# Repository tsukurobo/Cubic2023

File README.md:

**目次**

- [Cubic2023](#cubic2023)
  - [概要](#概要)
    - [コメント](#コメント)
- [Cubic2023\_Shield](#cubic2023_shield)
  - [概要](#概要-1)
    - [encoder pull up](#encoder-pull-up)
    - [increment encoder cognition](#increment-encoder-cognition)
    - [inverter(NOT)](#inverternot)
    - [increment RP2040](#increment-rp2040)
    - [increment connecter](#increment-connecter)
    - [absolute encoder cognition](#absolute-encoder-cognition)
    - [absolute RP2040](#absolute-rp2040)
    - [absolute connector](#absolute-connector)
    - [decoupling capacitor](#decoupling-capacitor)
    - [Arduino nano 33 BLE](#arduino-nano-33-ble)
    - [to MotherBoard](#to-motherboard)
- [Cubic2023\_DCMotorDriver](#cubic2023_dcmotordriver)
  - [概要](#概要-2)
    - [connector](#connector)
    - [pull down](#pull-down)
    - [A3921](#a3921)
    - [current sensor](#current-sensor)
    - [Filter](#filter)
    - [DeadTime](#deadtime)
    - [Protection Circuit](#protection-circuit)
    - [for motor connection](#for-motor-connection)
    - [Bootstrap Chargepump](#bootstrap-chargepump)
    - [Indication Circuit](#indication-circuit)
    - [V5 Circuit](#v5-circuit)
    - [Decoupling Condenser](#decoupling-condenser)
    - [Bridge](#bridge)
    - [pull up](#pull-up)
    - [error lamp](#error-lamp)
    - [PS](#ps)
    - [BD63150](#bd63150)
    - [Protection Circuit](#protection-circuit-1)
    - [Indication Circuit](#indication-circuit-1)
    - [VREF](#vref)
    - [for solenoid valve](#for-solenoid-valve)
- [Cubic2023\_RP2040](#cubic2023_rp2040)
  - [概要](#概要-3)
    - [RP2040](#rp2040)
    - [bypass condenser](#bypass-condenser)
    - [surge protection](#surge-protection)
    - [connector](#connector-1)
    - [indicator](#indicator)
    - [RESET switch](#reset-switch)
    - [microUSB](#microusb)
    - [QSPI NOR flash](#qspi-nor-flash)
    - [crystal](#crystal)

# Cubic2023

## 概要
つくばろぼっとサークルではNHK学生ロボコンに向けて統合型基板を製作しており、mainがNHK学生ロボコン2023において使用したバージョンです。
回路図の説明やブロック分けなどが出来ておらず、分かりにくい状態です。※修正中

### コメント
修正中です。8/10程度を目途に進めています。

# Cubic2023_Shield
## 概要
メインマイコンを搭載する基板です。メインマイコンには以下の理由からArduino nano 33 BLE(以下：AN33BLE)を採用しました。
- 32bitマイコン
- 浮動小数点演算ユニット搭載
- 書き込み環境の構築が容易

また、AN33BLEはIMUを搭載している点もメリットです。実際には用いていないため精度は不明ですが、基板面積という点では確実にプラスです。

センサとしては、8つのインクリメンタルエンコーダと8つのアブソリュートエンコーダを接続できるように設計しました。

### encoder pull up
インクリメントエンコーダに接続しているA相B相Z相をプルアップしています。

### increment encoder cognition
インクリメントエンコーダは、Z相の多くの範囲でLOWを返すため、NOT回路によりHIGHになり、LEDが光る仕組みです。Z相をプルアップしてるため、未接続の場合LEDは光りません。A相B相が断線してる場合、LEDは光りますが正常に認識されるとは限りません。何番のエンコーダに接続してるか簡易的に確認するための機能です。

### inverter(NOT)
インクリメントエンコーダの波形を整形するインバータ（バッファ）です。NOT回路と等価なので信号が反転します。A相B相は反転しても大きな影響はないですが、Z相はhighの時間が長くなります。長い信号線を介してセンシングするためチャタリング防止などの観点から挿入しました。また、5VトレラントのICを介することで5V信号を3.3Vで駆動するRP2040に入力できるようにしています。

### increment RP2040
インクリメントエンコーダを読み取り値を記録、メインマイコンの要求に応じて状態を返すためのマイコンです。インクリメントエンコーダの読み取りは割り込み処理を必要とするため、メインマイコンと分離したいと考え、この設計にしました。

### increment connecter
ラッチ付かつサイズが小さいコネクタが望ましかったため、PAコネクタを採用しました。**AMT102/103**を接続することを想定して、ピンの順番を設定しています。

### absolute encoder cognition
アブソリュートエンコーダとのSPI通信が確立した場合にRP2040がGPIOを操作しLEDを点灯させることが出来るようにしました。

### absolute RP2040
アブソリュートエンコーダと通信をして値を記録、メインマイコンの要求に応じて状態を返すためのマイコンです。メインマイコンをmasterとしたSPIバスとは別に、absolute RP2040をmasterとしたエンコーダとの通信用のSPIバスを用意しています。

### absolute connector
こちらもPAコネクタを採用しています。**AMT223**を接続することを想定して、ピンの順番を設定しています。

### decoupling capacitor
基板上のICなどのバイパスコンデンサです。配線を引き延ばすためエンコーダのコネクタ近くにも配置しました。

### Arduino nano 33 BLE
メインマイコンです。enableをHIGHにすることでシステムを起動することができます。RESETをLOWにすることでエンコーダ用のRP2040をリセットさせることできます。他はSPI通信用のGPIOです。

### to MotherBoard
電源、SPI通信、シャットダウン信号を共有しています。

### emergency shutdown
緊急停止スイッチ接続することでシステムを起動できます。LEDにより起動状態を表示しています。

### 3-state buffer
SPI通信のslave側は通信していないときはMISOをオープンにする仕様ですが、RP2040はLOWを出力してしまい、複数slave運用がデフォルトで不可能であったため、3-state bufferを付加することで対策しました。

# Cubic2023_DCMotorDriver
## 概要
RZ-735クラスのDCモータを2基、RS-555クラスのDCモータを1基、24Vで駆動することが出来る基板です。以下ではRZ-735を想定したチャネルをメインチャネル、他方をサブチャネルと呼称します。

メインチャネルではICにA3921を採用しています。サブチャネルではICにBD63150を採用しています。データシートを参考に作成しました。データシートに載っている内容は説明を省略します。

サブチャネルはハーフブリッジ×2と見なすことで電磁弁を制御することも出来ます。

https://www.allegromicro.com/ja-jp/products/motor-drivers/brush-dc-motor-drivers/a3921

https://www.rohm.co.jp/products/motor-actuator-drivers/dc-brush-motor/bd63150afm-product

### connector
電流センサのアナログ値伝送用に4pin、信号・降圧電源用に14pin、VDDとGNDPWRに各14pinでMotherBoardと接続します。GNDは信号用と電源用で分離しています。

### pull down
MotherBoardからの信号がない場合の誤動作防止のためにプルダウン抵抗を挿入しています。

### A3921
Cissの大きいMOSFETを容易に駆動できる便利なICです。SR,PWMLにhighを入力、pwmhにPWM、phaseにhigh/lowを入力することで、SMB方式でモータを駆動できます。

### current sensor
メインチャネルを電流制御するために搭載した電流センサICです。コスト面からACS712を採用しましたが、動作を確認したところ、ノイズの影響で大きかったため、現状電流を用いた制御は実装していません。

### Filter
MotherBoardに大容量の電解コンデンサを搭載していますが、ピンヘッダを経由するため補助として中容量の電解コンデンサを搭載しています。

### DeadTime
$$ 50+\frac{7200}{1.2+(200/Rdead[kΩ])} $$
datasheet上の数式に従いdeadtimeが2300nsになるように抵抗値を設定しました。

### Protection Circuit
RCスナバ回路と双方向ツェナーダイオードによる保護回路を搭載しています。RCスナバ回路の値は以下の式に基づいて決定しました。回路を解析して搭載したわけではなく、簡易的な計算から求めているため効果は薄いと思います。

$$ Rsnb = \frac{Vin}{Iin} = \frac{24[V]}{2.4[A]} = 10[Ω] $$
$$ Csnb = \frac{Prsnb}{f×{Vin}^2} = \frac{0.1[W]}{60k[Hz]×{24[V]}^2} = 2.89n[F] $$

$$ Iin:想定電流, Prsnb：スナバ抵抗の定格電力, f:MD動作周波数$$
※想定電流は実際より小さめ、MD動作周波数は実際より大きめの値で計算されてます。設計初期の名残です。

モーターの逆起電力からMDを保護するために降伏電圧が28Vの双方向ツェナーダイオード（TVS）を採用しています。

**注：現行基板では、逆起電力から保護しきれていないことが原因と思われるA3921の破壊が確認されています。**

### for motor connection
モーターに接続する端子です。

### Bootstrap Chargepump
DCバイアスを考慮してコンデンサを配置しました。

### Indication Circuit
モーターに接続している箇所にLEDを対面配置することで回転方向を表示しています。プログラム開発時に便利でした。ローサイドMOSFETのゲート端子にデバッグ用のLEDを配置しています。ICが壊れた場合に表示されなくなるのでデバッグに活用できました。

|  LEDの色  |  用途  |
| ---- | ---- |
|  緑  |  常時点灯  |
|  青  |  電源ON＆正常時点灯  |
|  赤  |  異常時点灯  |
|  黄  |  状態表示  |
|  白  |  状態表示  |

### V5 Circuit
A3921に搭載されている5Vレギュレータを利用してA3921搭載のエラーLEDを配置しています。また、VDSTHに送る電圧を分圧で生成しています。

### Decoupling Condenser
ブートストラップコンデンサの容量が大きく、A3921の挙動が不安定になることがあったので、10uFのコンデンサを搭載しました。

### Bridge
フルブリッジ回路です。前述のRCスナバ回路を搭載しています。MOSFETは**RJ1L12BGN**を採用しています。corestaffで購入すると比較的安価に購入可能です。ON抵抗は小さいですが、ゲート容量は大きいので気を付けてください。新規設計する場合は**RS6L120BG**がおすすめです。ゲート抵抗には27Ωを採用しました。この抵抗値にした理由は勘です。

簡易的ではありますが以下の式で計算可能です。
$$ \frac{Vg}{Imax} < Rg < \frac{Tdead}{3×Ciss}$$
$$ Rg:ゲート抵抗,Vg:ゲート駆動電圧,Imax:ICがゲートに流せる最大電流,Tdead:デッドタイム,Ciss:MOSFET入力容量　$$
※条件によっては解なしになるかと思います。

### pull up
MDへの入力信号をプルアップしています。

### error lamp
BD63150のエラー表示用のLEDです。

### PS
PowerSaveに繋いでる端子です。プルアップしています。

### BD63150
電圧制御・電流制限に対応したモータードライバICです。RFNには100mΩのシャント抵抗を搭載しています。3Aで電流制限をする計算でしたが、想定より厳しめに作動していました。恐らくGNDを信号とパワーで分離した弊害だと思われます。

### Protection Circuit
メインチャネルと同様の構成です。

### Indication Circuit
メインチャネルと同様の構成です。

### VREF
電流の制限値をICに入力するピンです。3Aで制限するように設定したのですが、前述の通り思うように動きませんでした。

### for solenoid valve
電磁弁を駆動できるように付加した回路です。セーフティとしてリセッタブルヒューズを載せています。また還流ダイオードも載せています。

# Cubic2023_RP2040
## 概要
Cubicでは以下の理由から組み込みマイコンにRP2040を採用しました。
- GPIOとPWMが多い
- cortex-M0（計算速度がそこそこ速い）
- 安価
- 書き込みが容易

システム内で3つ使い、容易に交換可能とするためにマイコンボードとして最小構成の基板を作成しました。

以下の公式リファレンスを参考に作成しました。公式リファレンスに載っている内容は説明を省略します。
https://datasheets.raspberrypi.com/rp2040/hardware-design-with-rp2040.pdf

### RP2040
RP2040と周辺の配線です。
### bypass condenser
マイコンの電力消費が多く動作が不安定になることがあったため、100uFのセラコンを追加しています。
### surge protection
システム内でモータドライバと絶縁せずにRP2040を用いている箇所があるため、サージ保護としてツェナーダイオードを電源に並列に繋いでいます。
### connector
基板サイズの制約の中でGPIOをフルに使う必要があり、1.27mmピッチのピンヘッダを採用しました。配線の最適化と差し込みの一意性を担保するために基板の3辺に沿うように配置しています。
### indicator
基板内通信にSPIを利用しているのですが、SPI通信の状態を外部から容易に観測するためにslave側のSSに該当する箇所にLEDを付けています。以下は目視のLED状態とSSに注意したSPI通信の状況です。
|  LED  |  状況  |
| ---- | ---- |
|  点灯  |  通信異常  |
|  僅かに点灯  |  正常  |
|  点滅  |  通信速度低  |
|  消灯  |  オフライン  |

### RESET switch
RP2040をリセットできます。接続先がMotherBoardの場合は、接続先もリセットされます。

### microUSB
RP2040にプログラムを書き込むmicroUSBです。基本的に動作中の電源は接続先の基板から受け取るため、RP2040に書き込む以外は使用しない想定です。

### QSPI NOR flash
プログラムが書き込まれるメモリです。

### crystal
RP2040動作のためのcrystalです。

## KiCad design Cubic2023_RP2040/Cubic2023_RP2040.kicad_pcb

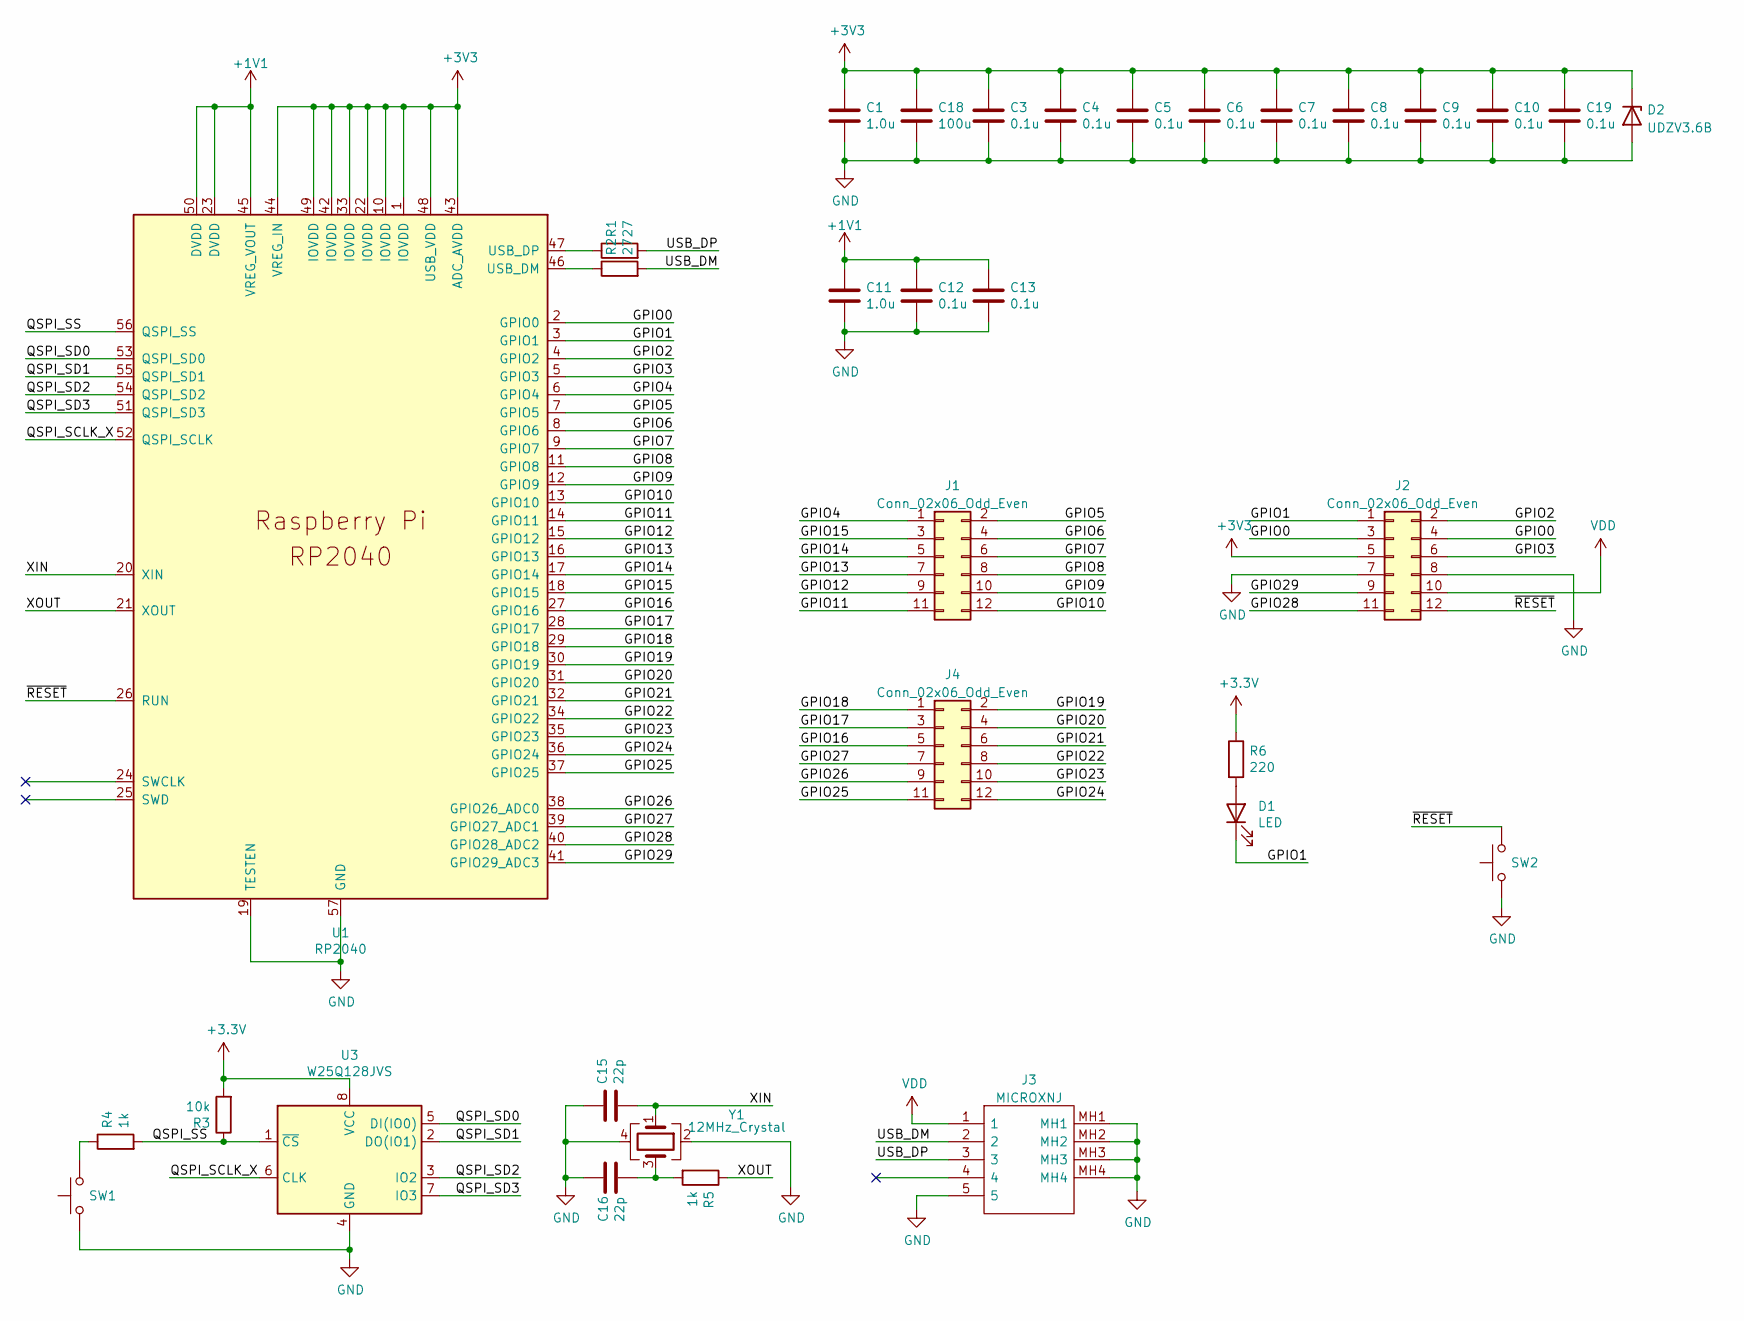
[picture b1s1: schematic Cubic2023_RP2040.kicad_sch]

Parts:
C1, C11: 1.0u; C_0805_2012Metric; LCSC C28323
C3, C4, C5, C6, C7, C8, C9, C10, C12, C13, C19: 0.1u; C_0402_1005Metric_Pad0.74x0.62mm_HandSolder; LCSC C307331
C15, C16: 22p; C_0402_1005Metric_Pad0.74x0.62mm_HandSolder; LCSC C1555
C18: 100u; C_1206_3216Metric; LCSC C15008
D1: LED; LED_0603_1608Metric_Pad1.05x0.95mm_HandSolder; LCSC C72041
D2: UDZV3.6B; D_SOD-323_HandSoldering
J1, J2, J4: Conn_02x06_Odd_Even; PinHeader_2x06_P1.27mm_Vertical
J3: MICROXNJ; Manufacturer_Part_Number MICROXNJ; LCSC C404969
R1, R2: 27; R_0603_1608Metric; LCSC C25190
R3: 10k; R_0603_1608Metric; LCSC C25804
R4, R5: 1k; R_0603_1608Metric; LCSC C21190
R6: 220; R_0603_1608Metric; LCSC C22962
SW1, SW2: SW_Push; SW_DIP_SPSTx01_Slide_9.78x4.72mm_W7.62mm_P2.54mm
U1: RP2040; RP2040-QFN-56; LCSC C2040
U3: W25Q128JVS; SOIC-8_5.23x5.23mm_P1.27mm; LCSC C97521
Y1: 12MHz_Crystal; Crystal_SMD_3225-4Pin_3.2x2.5mm; LCSC C9002

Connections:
+1V1: C11.1, C12.1, C13.1, U1.23 (DVDD), U1.45 (VREG_VOUT), U1.50 (DVDD)
/GPIO0: J2.3, J2.4, U1.2 (GPIO0)
/GPIO1: D1.1 (K), J2.1, U1.3 (GPIO1)
/GPIO2: J2.2, U1.4 (GPIO2)
/GPIO3: J2.6, U1.5 (GPIO3)
/GPIO4: J1.1, U1.6 (GPIO4)
/GPIO5: J1.2, U1.7 (GPIO5)
/GPIO6: J1.4, U1.8 (GPIO6)
/GPIO7: J1.6, U1.9 (GPIO7)
/GPIO8: J1.8, U1.11 (GPIO8)
/GPIO9: J1.10, U1.12 (GPIO9)
/GPIO10: J1.12, U1.13 (GPIO10)
/GPIO11: J1.11, U1.14 (GPIO11)
/GPIO12: J1.9, U1.15 (GPIO12)
/GPIO13: J1.7, U1.16 (GPIO13)
/GPIO14: J1.5, U1.17 (GPIO14)
/GPIO15: J1.3, U1.18 (GPIO15)
/GPIO16: J4.5, U1.27 (GPIO16)
/GPIO17: J4.3, U1.28 (GPIO17)
/GPIO18: J4.1, U1.29 (GPIO18)
/GPIO19: J4.2, U1.30 (GPIO19)
/GPIO20: J4.4, U1.31 (GPIO20)
/GPIO21: J4.6, U1.32 (GPIO21)
/GPIO22: J4.8, U1.34 (GPIO22)
/GPIO23: J4.10, U1.35 (GPIO23)
/GPIO24: J4.12, U1.36 (GPIO24)
/GPIO25: J4.11, U1.37 (GPIO25)
/GPIO26: J4.9, U1.38 (GPIO26_ADC0)
/GPIO27: J4.7, U1.39 (GPIO27_ADC1)
/GPIO28: J2.11, U1.40 (GPIO28_ADC2)
/GPIO29: J2.9, U1.41 (GPIO29_ADC3)
/QSPI_SCLK_X: U1.52 (QSPI_SCLK), U3.6 (CLK)
/QSPI_SD0: U1.53 (QSPI_SD0), U3.5 (DI(IO0))
/QSPI_SD1: U1.55 (QSPI_SD1), U3.2 (DO(IO1))
/QSPI_SD2: U1.54 (QSPI_SD2), U3.3 (IO2)
/QSPI_SD3: U1.51 (QSPI_SD3), U3.7 (IO3)
/QSPI_SS: R3.1, R4.2, U1.56 (QSPI_SS), U3.1 (~CS)
/USB_DM: J3.2, R2.2
/USB_DP: J3.3, R1.2
/XIN: C15.2, U1.20 (XIN), Y1.1
/XOUT: R5.1, U1.21 (XOUT)
/~RESET: J2.12, SW2.2, U1.26 (RUN)
GND: C1.2, C3.2, C4.2, C5.2, C6.2, C7.2, C8.2, C9.2, C10.2, C11.2, C12.2, C13.2, C15.1, C16.1, C18.2, C19.2, D2.2 (A), J2.7, J2.8, J3.5, J3.MH1, J3.MH2, J3.MH3, J3.MH4, SW1.1, SW2.1, U1.19 (TESTEN), U1.57 (GND), U3.4 (GND), Y1.2, Y1.4
unnamed: D1.2 (A), R6.2
unnamed: R1.1, U1.47 (USB_DP)
unnamed: R2.1, U1.46 (USB_DM)
unnamed: R4.1, SW1.2
unnamed: C16.2, R5.2, Y1.3
VDD: J2.10, J3.1

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
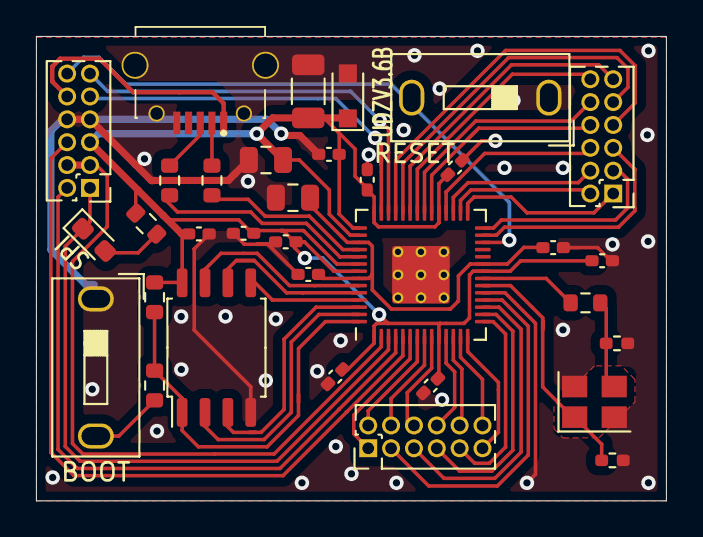
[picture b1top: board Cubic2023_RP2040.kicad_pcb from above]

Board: 2 copper layers, 35.0 x 25.8 mm, 33 parts (0 on the bottom side), 50 nets.

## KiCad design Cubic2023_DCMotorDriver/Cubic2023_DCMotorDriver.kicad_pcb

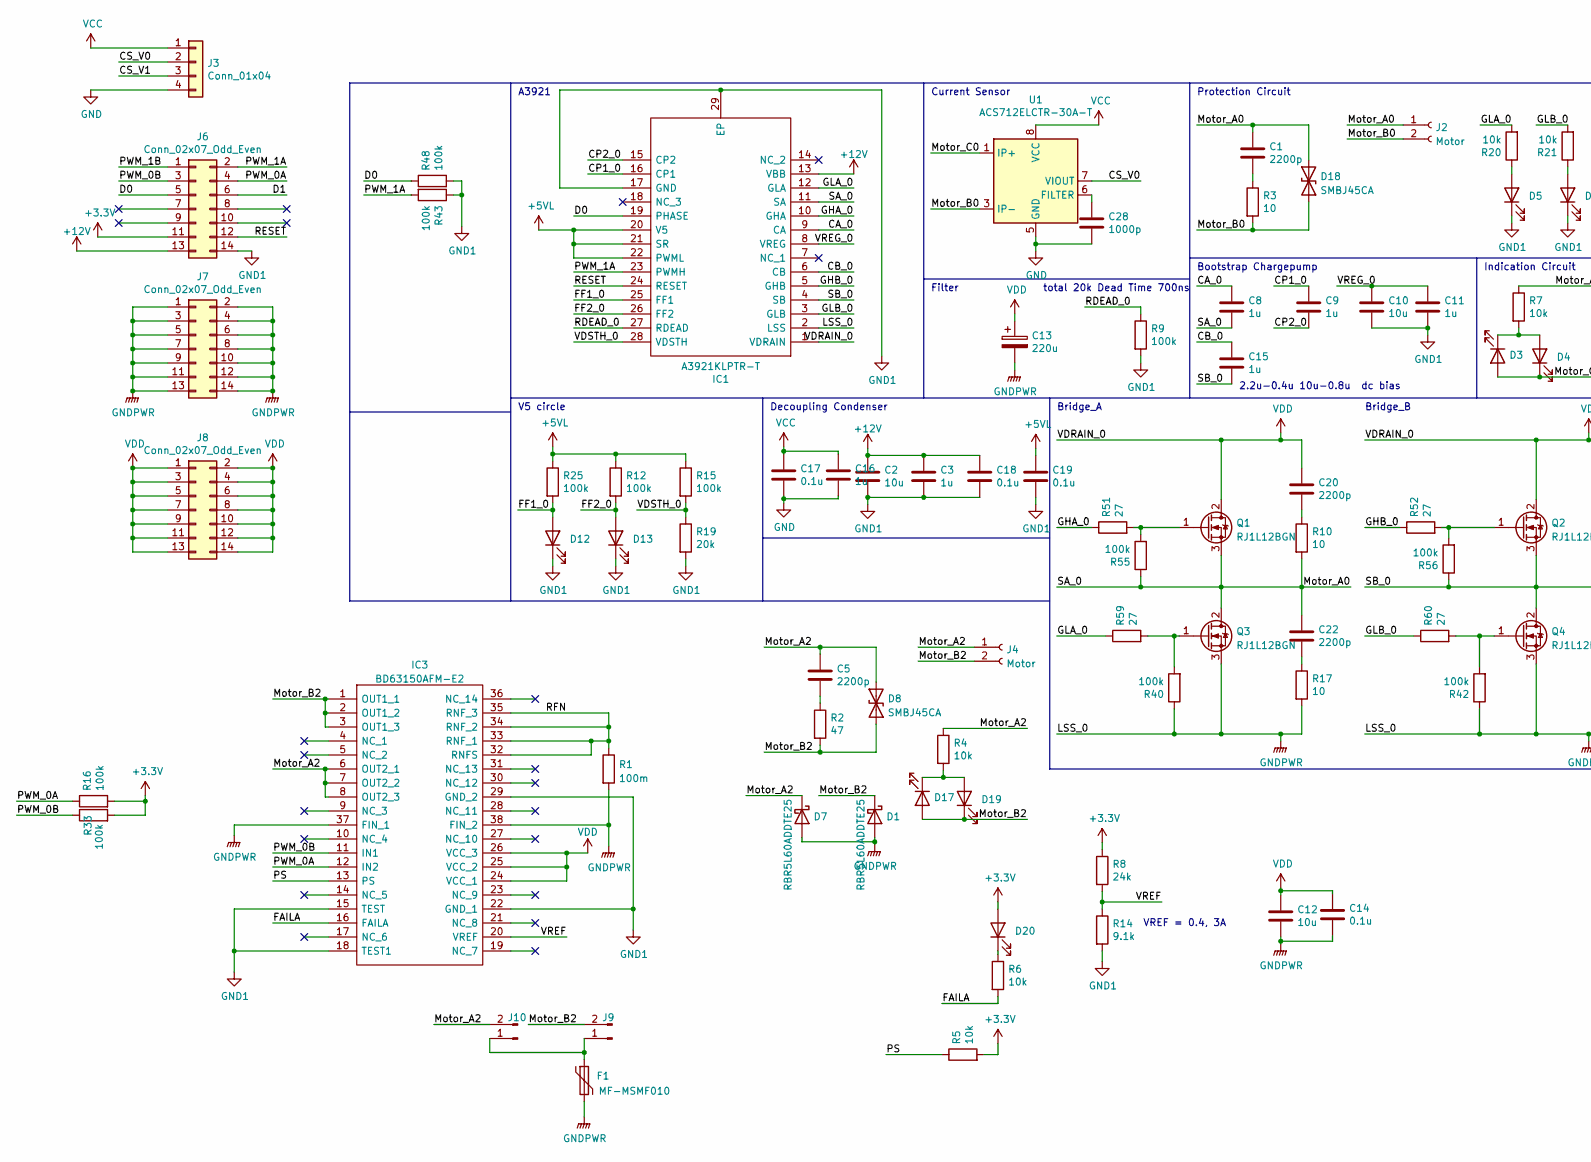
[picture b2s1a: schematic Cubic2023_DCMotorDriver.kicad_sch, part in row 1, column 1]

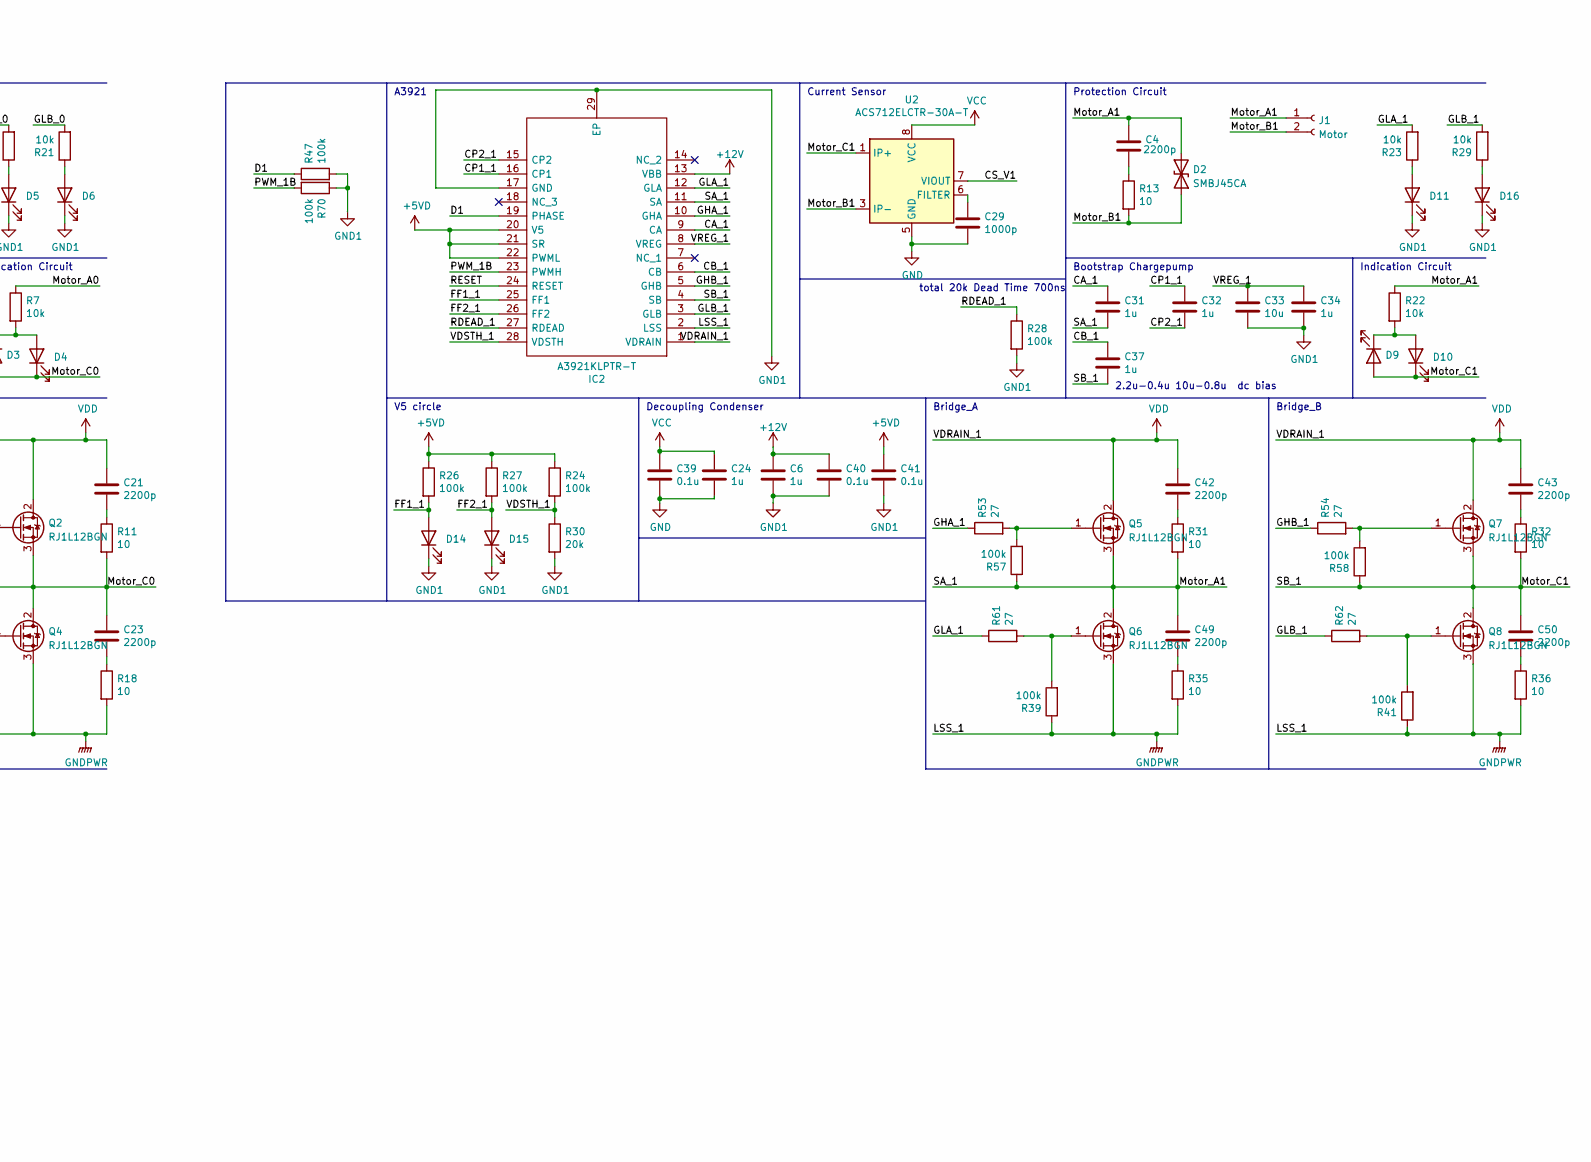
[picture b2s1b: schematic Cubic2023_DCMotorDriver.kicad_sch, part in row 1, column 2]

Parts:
C1, C4, C5, C20, C21, C22, C23, C42, C43, C49, C50: 2200p; R_0603_1608Metric; LCSC C1604
C2, C10, C12, C33: 10u; C_1206_3216Metric; LCSC C13585
C3, C6, C8, C9, C11, C15, C16, C24, C31, C32, C34, C37: 1u; R_0603_1608Metric; LCSC C15849
C13: 220u; CP_Elec_10x10.5
C14, C17, C18, C19, C39, C40, C41: 0.1u; C_0402_1005Metric_Pad0.74x0.62mm_HandSolder; LCSC C307331
C28, C29: 1000p; R_0603_1608Metric; LCSC C1588
D1, D7: RBR5L60ADDTE25; D_SMA
D2, D8, D18: SMBJ45CA; D_SMB; LCSC C353357
D3, D9, D17: LED_White; D_0603_1608Metric_Pad1.05x0.95mm_HandSolder; LCSC C2290
D4, D10, D19: LED_Yellow; D_0603_1608Metric_Pad1.05x0.95mm_HandSolder; LCSC C72038
D5, D6, D11, D16: LED_Blue; D_0603_1608Metric_Pad1.05x0.95mm_HandSolder; LCSC C72041
D12, D13, D14, D15, D20: LED_Red; D_0603_1608Metric_Pad1.05x0.95mm_HandSolder; LCSC C2286
F1: MF-MSMF010; Fuse_1812_4532Metric; LCSC C12430
IC1, IC2: A3921KLPTR-T; HTSSOP-28-1EP_4.4x9.7mm_P0.65mm_EP2.85x5.4mm_ThermalVias; Manufacturer_Part_Number A3921KLPTR-T
IC3: BD63150AFM-E2; BD63150AFME2; Manufacturer_Part_Number BD63150AFM-E2; Mouser Part Number 755-BD63150AFM-E2
J1, J2, J4: Motor; T_plug_female
J3: Conn_01x04; PinHeader_1x04_P2.54mm_Horizontal
J6, J7, J8: Conn_02x07_Odd_Even; PinHeader_2x07_P2.54mm_Horizontal
J9, J10: Conn_01x02_Male; PinHeader_1x02_P2.00mm_Horizontal
Q1, Q2, Q3, Q4, Q5, Q6, Q7, Q8: RJ1L12BGN; TO-263-2
R1: 100m; R_2512_6332Metric; LCSC C2994646
R2: 47; R_0603_1608Metric; LCSC C23182
R3, R10, R11, R13, R17, R18, R31, R32, R35, R36: 10; R_0603_1608Metric; LCSC C22859
R4, R5, R6, R7, R20, R21, R22, R23, R29: 10k; R_0603_1608Metric; LCSC C25804
R8: 24k; R_0603_1608Metric; LCSC C23352
R9, R12, R15, R16, R24, R25, R26, R27, R28, R33, R39, R40, R41, R42, R43, R47, R48, R55, R56, R57, R58, R70: 100k; R_0603_1608Metric; LCSC C25803
R14: 9.1k; R_0603_1608Metric; LCSC C23260
R19, R30: 20k; R_0603_1608Metric; LCSC C4184
R51, R52, R53, R54, R59, R60, R61, R62: 27; R_0603_1608Metric; LCSC C25190
U1, U2: ACS712ELCTR-30A-T; SOP-8_3.9x4.9mm_P1.27mm

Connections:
+3V3: D20.2 (A), J6.11, R5.2, R8.1, R16.2, R33.2
+5VD: C41.1, IC2.20 (V5), IC2.21 (SR), IC2.22 (PWML), R24.1, R26.1, R27.1
+5VL: C19.1, IC1.20 (V5), IC1.21 (SR), IC1.22 (PWML), R12.1, R15.1, R25.1
+12V: C2.1, C3.1, C6.1, C18.1, C40.1, IC1.13 (VBB), IC2.13 (VBB), J6.13
/CA_0: C8.1, IC1.9 (CA)
/CA_1: C31.1, IC2.9 (CA)
/CB_0: C15.1, IC1.6 (CB)
/CB_1: C37.1, IC2.6 (CB)
/CP1_0: C9.1, IC1.16 (CP1)
/CP1_1: C32.1, IC2.16 (CP1)
/CP2_0: C9.2, IC1.15 (CP2)
/CP2_1: C32.2, IC2.15 (CP2)
/CS_V0: J3.2, U1.7 (VIOUT)
/CS_V1: J3.3, U2.7 (VIOUT)
/D0: IC1.19 (PHASE), J6.5, R48.1
/D1: IC2.19 (PHASE), J6.6, R47.1
/FAILA: IC3.16 (FAILA), R6.2
/FF1_0: D12.2 (A), IC1.25 (FF1), R25.2
/FF1_1: D14.2 (A), IC2.25 (FF1), R26.2
/FF2_0: D13.2 (A), IC1.26 (FF2), R12.2
/FF2_1: D15.2 (A), IC2.26 (FF2), R27.2
/GHA_0: IC1.10 (GHA), R51.1
/GHA_1: IC2.10 (GHA), R53.1
/GHB_0: IC1.5 (GHB), R52.1
/GHB_1: IC2.5 (GHB), R54.1
/GLA_0: IC1.12 (GLA), R20.2, R59.1
/GLA_1: IC2.12 (GLA), R23.2, R61.1
/GLB_0: IC1.3 (GLB), R21.2, R60.1
/GLB_1: IC2.3 (GLB), R29.2, R62.1
/Motor_A0: C1.1, C8.2, C22.1, D18.2 (A2), IC1.11 (SA), J2.1, Q1.3 (S), Q3.2 (D), R7.1, R10.2, R55.1
/Motor_A1: C4.1, C31.2, C49.1, D2.2 (A2), IC2.11 (SA), J1.1, Q5.3 (S), Q6.2 (D), R22.1, R31.2, R57.1
/Motor_A2: C5.1, D7.1 (K), D8.2 (A2), IC3.6 (OUT2_1), IC3.7 (OUT2_2), IC3.8 (OUT2_3), J4.1, J10.2, R4.1
/Motor_B0: D18.1 (A1), J2.2, R3.2, U1.3 (IP-), U1.4 (IP-)
/Motor_B1: D2.1 (A1), J1.2, R13.2, U2.3 (IP-), U2.4 (IP-)
/Motor_B2: D1.1 (K), D8.1 (A1), D17.2 (A), D19.1 (K), IC3.1 (OUT1_1), IC3.2 (OUT1_2), IC3.3 (OUT1_3), J4.2, J9.2, R2.2
/Motor_C0: C15.2, C23.1, D3.2 (A), D4.1 (K), IC1.4 (SB), Q2.3 (S), Q4.2 (D), R11.2, R56.1, U1.1 (IP+), U1.2 (IP+)
/Motor_C1: C37.2, C50.1, D9.2 (A), D10.1 (K), IC2.4 (SB), Q7.3 (S), Q8.2 (D), R32.2, R58.1, U2.1 (IP+), U2.2 (IP+)
/PS: IC3.13 (PS), R5.1
/PWM_0A: IC3.12 (IN2), J6.4, R16.1
/PWM_0B: IC3.11 (IN1), J6.3, R33.1
/PWM_1A: IC1.23 (PWMH), J6.2, R43.2
/PWM_1B: IC2.23 (PWMH), J6.1, R70.2
/RDEAD_0: IC1.27 (RDEAD), R9.1
/RDEAD_1: IC2.27 (RDEAD), R28.1
/RESET: IC1.24 (RESET), IC2.24 (RESET), J6.12
/RFN: IC3.32 (RNFS), IC3.33 (RNF_1), IC3.34 (RNF_2), IC3.35 (RNF_3), R1.1
/VDSTH_0: IC1.28 (VDSTH), R15.2, R19.1
/VDSTH_1: IC2.28 (VDSTH), R24.2, R30.1
/VREF: IC3.20 (VREF), R8.2, R14.1
/VREG_0: C10.1, C11.1, IC1.8 (VREG)
/VREG_1: C33.1, C34.1, IC2.8 (VREG)
GND: C16.2, C17.2, C24.2, C28.2, C29.2, C39.2, J3.4, U1.5 (GND), U2.5 (GND)
GND1: C2.2, C3.2, C6.2, C10.2, C11.2, C18.2, C19.2, C33.2, C34.2, C40.2, C41.2, D5.1 (K), D6.1 (K), D11.1 (K), D12.1 (K), D13.1 (K), D14.1 (K), D15.1 (K), D16.1 (K), IC1.17 (GND), IC1.29 (EP), IC2.17 (GND), IC2.29 (EP), IC3.15 (TEST), IC3.18 (TEST1), IC3.22 (GND_1), IC3.29 (GND_2), J6.14, R9.2, R14.2, R19.2, R28.2, R30.2, R43.1, R47.2, R48.2, R70.1
GNDPWR: C12.2, C13.2, C14.2, D1.2 (A), D7.2 (A), F1.2, IC1.2 (LSS), IC2.2 (LSS), IC3.37 (FIN_1), IC3.38 (FIN_2), J7.1, J7.2, J7.3, J7.4, J7.5, J7.6, J7.7, J7.8, J7.9, J7.10, J7.11, J7.12, J7.13, J7.14, Q3.3 (S), Q4.3 (S), Q6.3 (S), Q8.3 (S), R1.2, R17.2, R18.2, R35.2, R36.2, R39.1, R40.1, R41.1, R42.1
unnamed: C1.2, R3.1
unnamed: C4.2, R13.1
unnamed: C5.2, R2.1
unnamed: C20.2, R10.1
unnamed: C21.2, R11.1
unnamed: C22.2, R17.1
unnamed: C23.2, R18.1
unnamed: C28.1, U1.6 (FILTER)
unnamed: C29.1, U2.6 (FILTER)
unnamed: C42.2, R31.1
unnamed: C43.2, R32.1
unnamed: C49.2, R35.1
unnamed: C50.2, R36.1
unnamed: D3.1 (K), D4.2 (A), R7.2
unnamed: D5.2 (A), R20.1
unnamed: D6.2 (A), R21.1
unnamed: D9.1 (K), D10.2 (A), R22.2
unnamed: D11.2 (A), R23.1
unnamed: D16.2 (A), R29.1
unnamed: D17.1 (K), D19.2 (A), R4.2
unnamed: D20.1 (K), R6.1
unnamed: F1.1, J9.1, J10.1
unnamed: Q1.1 (G), R51.2, R55.2
unnamed: Q2.1 (G), R52.2, R56.2
unnamed: Q3.1 (G), R40.2, R59.2
unnamed: Q4.1 (G), R42.2, R60.2
unnamed: Q5.1 (G), R53.2, R57.2
unnamed: Q6.1 (G), R39.2, R61.2
unnamed: Q7.1 (G), R54.2, R58.2
unnamed: Q8.1 (G), R41.2, R62.2
VCC: C16.1, C17.1, C24.1, C39.1, J3.1, U1.8 (VCC), U2.8 (VCC)
VDD: C12.1, C13.1, C14.1, C20.1, C21.1, C42.1, C43.1, IC1.1 (VDRAIN), IC2.1 (VDRAIN), IC3.24 (VCC_1), IC3.25 (VCC_2), IC3.26 (VCC_3), J8.1, J8.2, J8.3, J8.4, J8.5, J8.6, J8.7, J8.8, J8.9, J8.10, J8.11, J8.12, J8.13, J8.14, Q1.2 (D), Q2.2 (D), Q5.2 (D), Q7.2 (D)

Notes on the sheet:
2.2u-0.4u 10u-0.8u dc bias
Decoupling Condenser
Bootstrap Chargepump
Filter
Current Sensor
Bridge_B
VREF = 0.4, 3A
V5 circle
Bridge_A
Indication Circuit
total 20k Dead Time 700ns
A3921
Protection Circuit

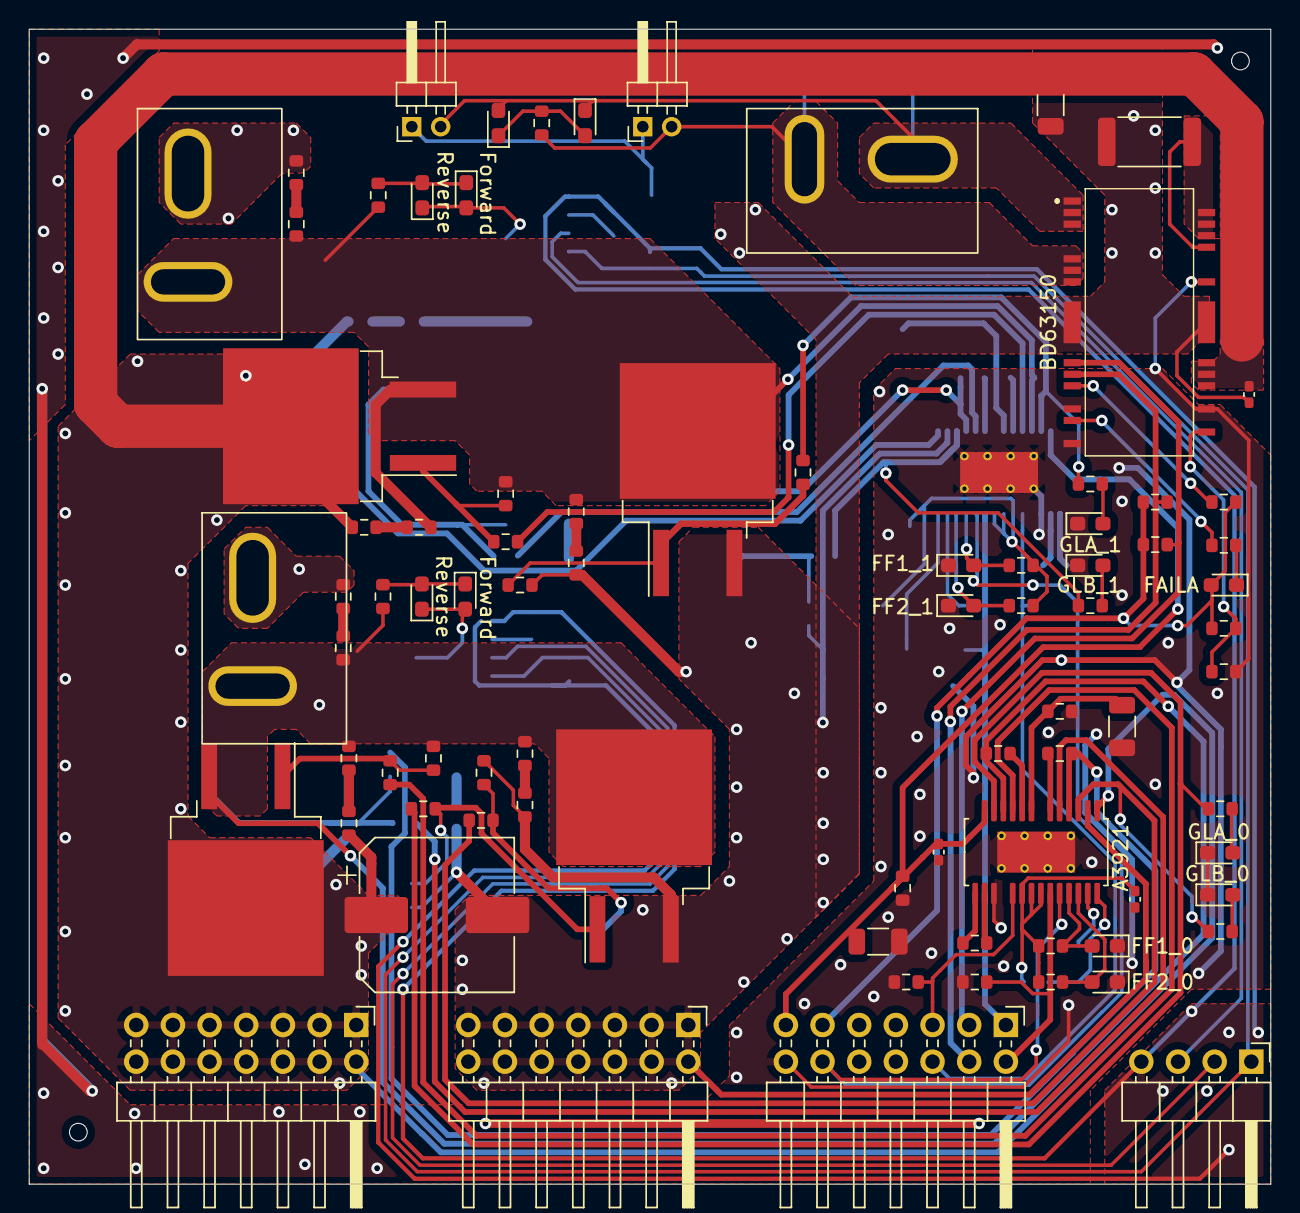
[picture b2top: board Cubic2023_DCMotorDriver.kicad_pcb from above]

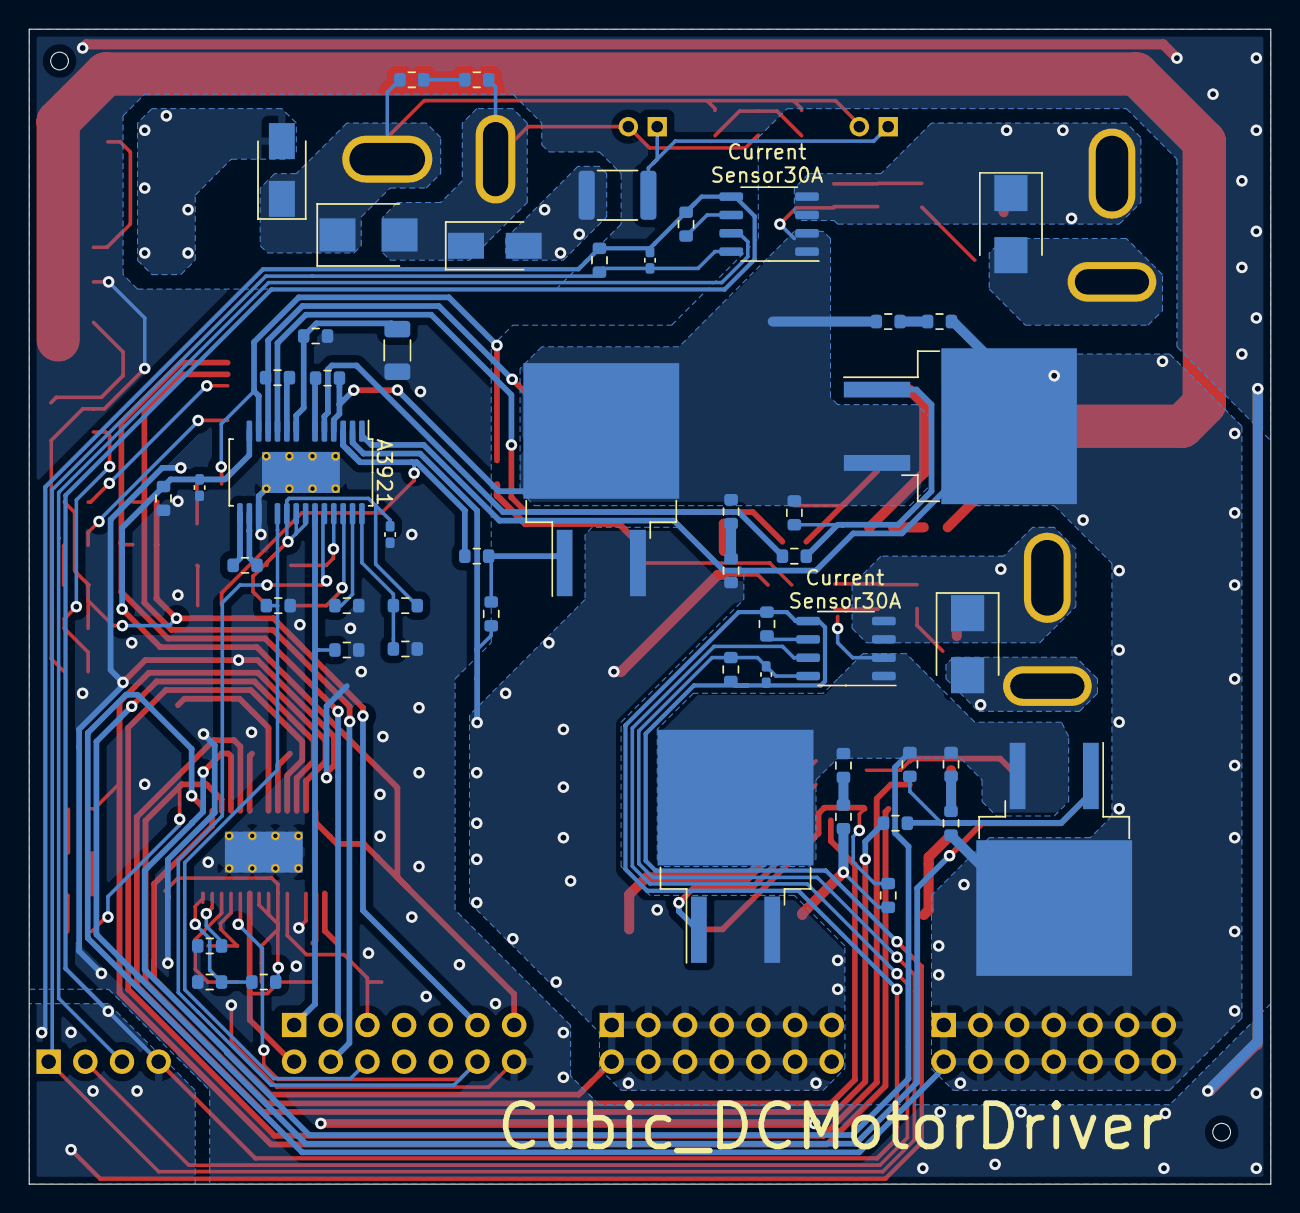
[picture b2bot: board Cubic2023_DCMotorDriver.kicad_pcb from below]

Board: 2 copper layers, 86.0 x 80.0 mm, 135 parts (52 on the bottom side), 86 nets.
